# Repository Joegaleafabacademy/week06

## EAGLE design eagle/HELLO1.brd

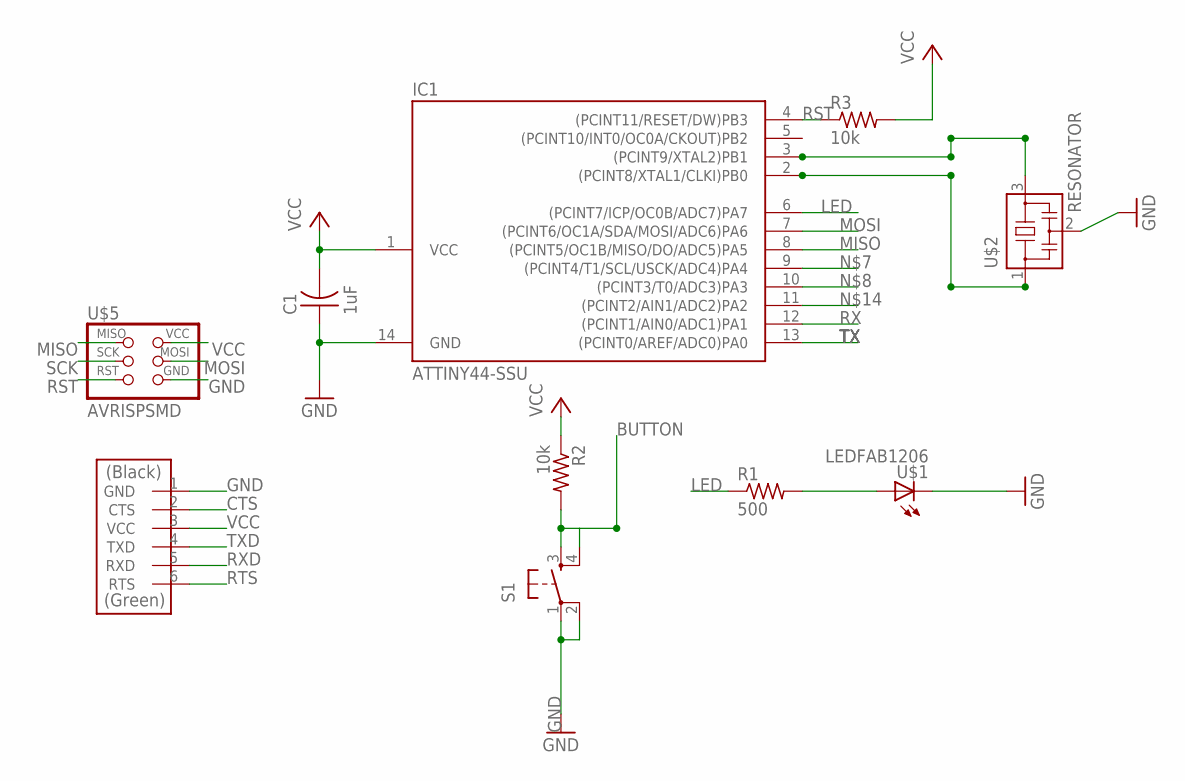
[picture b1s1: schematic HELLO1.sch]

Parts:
C1: 1uF; C1206FAB
IC1: ATTINY44-SSU; SOIC14
R1: 500; R1206FAB
R2, R3: 10k; R1206FAB
S1: 6MM_SWITCH6MM_SWITCH; 6MM_SWITCH
U$1: LEDFAB1206; LED1206FAB
U$2: RESONATOR; EFOBM
U$4: FTDI-SMD-HEADER; 1X06SMD
U$5: AVRISPSMD; 2X03SMD

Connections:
BUTTON: R2.2, S1.3 (S), S1.4 (S1)
CTS: U$4.2 (CTS)
GND: C1.1, IC1.14 (GND), S1.1, S1.2 (P1), U$1.2 (C), U$2.2, U$4.1 (GND), U$5.6 (GND)
LED: IC1.6 ((PCINT7/ICP/OC0B/ADC7)PA7), R1.1
MISO: IC1.8 ((PCINT5/OC1B/MISO/DO/ADC5)PA5), U$5.1 (MISO)
MOSI: IC1.7 ((PCINT6/OC1A/SDA/MOSI/ADC6)PA6), U$5.4 (MOSI)
unnamed: IC1.2 ((PCINT8/XTAL1/CLKI)PB0), U$2.1
unnamed: IC1.3 ((PCINT9/XTAL2)PB1), U$2.3
unnamed: R1.2, U$1.1 (A)
RST: IC1.4 ((PCINT11/RESET/DW)PB3), R3.1, U$5.5 (RST)
RTS: U$4.6 (RTS)
RX: IC1.12 ((PCINT1/AIN0/ADC1)PA1)
RXD: U$4.5 (RXD)
SCK: U$5.3 (SCK)
TX: IC1.13 ((PCINT0/AREF/ADC0)PA0)
TXD: U$4.4 (TXD)
VCC: C1.2, IC1.1 (VCC), R2.1, R3.2, U$4.3 (VCC), U$5.2 (VCC)

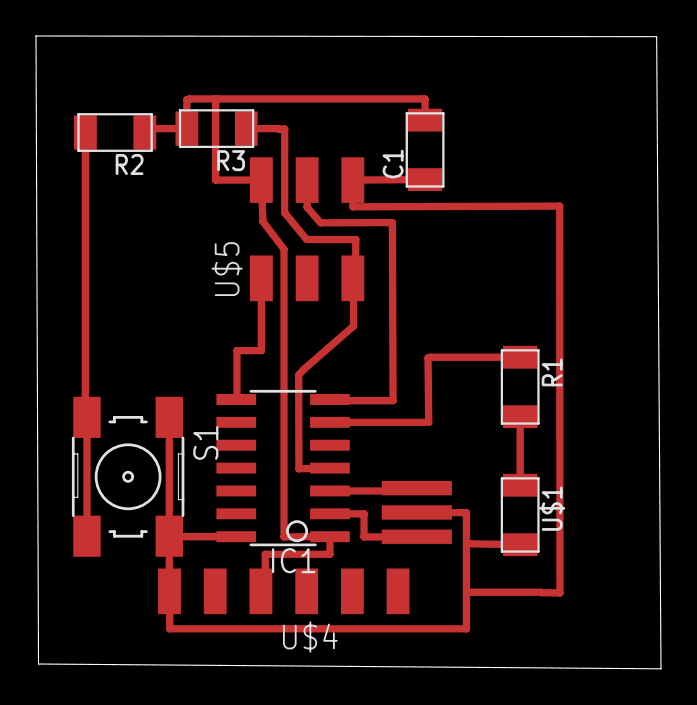
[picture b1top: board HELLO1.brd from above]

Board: 2 copper layers, 34.7 x 35.2 mm, 10 parts (0 on the bottom side), 10 nets.

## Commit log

2016-06-05 Electronic design
